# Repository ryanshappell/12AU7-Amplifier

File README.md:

# 12AU7-Amplifier
12AU7 Vacuum tube headphone amplifier.

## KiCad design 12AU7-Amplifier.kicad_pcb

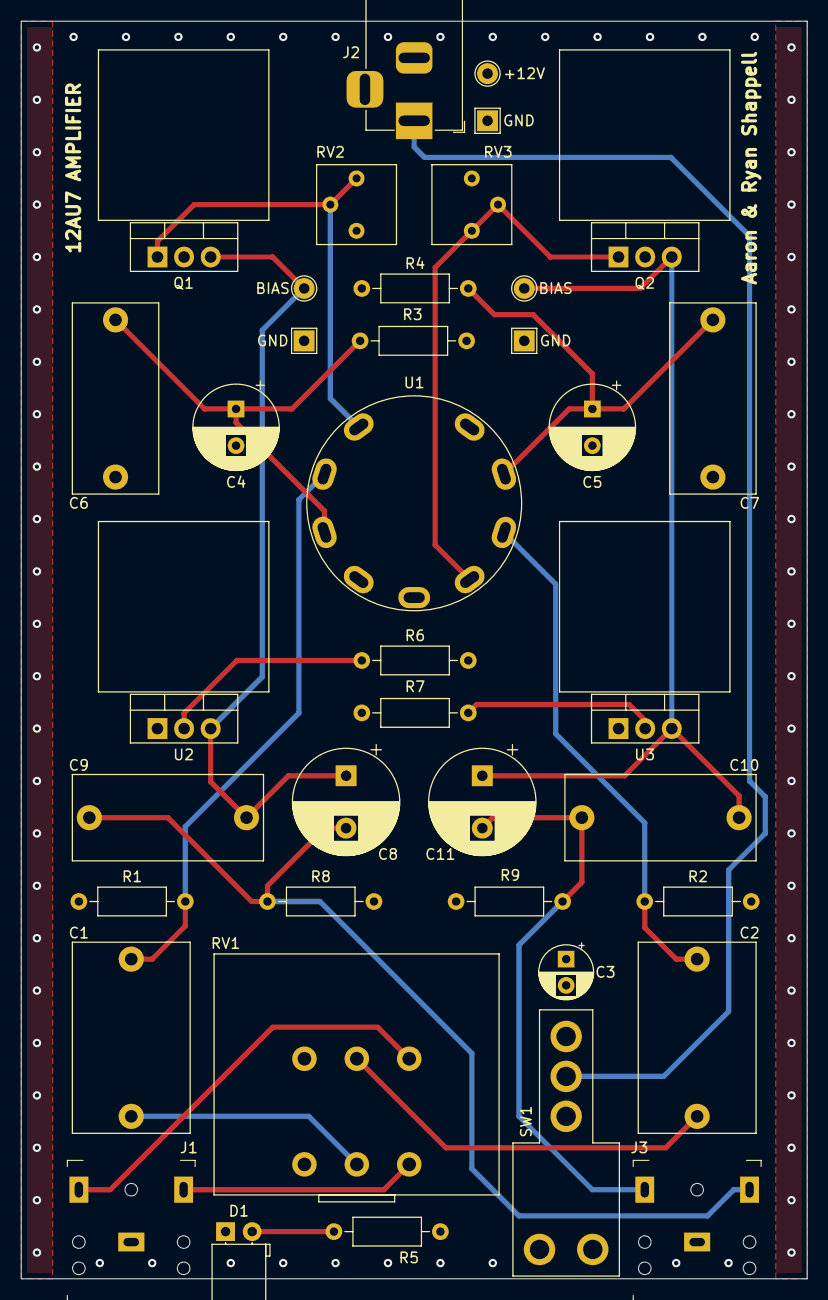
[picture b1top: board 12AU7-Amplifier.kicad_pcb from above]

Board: 4 copper layers, 75.0 x 120.0 mm, 39 parts (0 on the bottom side), 20 nets.

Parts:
C1, C2: 2.2u; C_Rect_L18.0mm_W11.0mm_P15.00mm_FKS3_FKP3
C3: 10uF; CP_Radial_D5.0mm_P2.50mm
C4, C5: 100u; CP_Radial_D8.0mm_P3.50mm
C6, C7, C9, C10: 1u; C_Rect_L18.0mm_W8.0mm_P15.00mm_FKS3_FKP3
C8, C11: 470u; CP_Radial_D10.0mm_P5.00mm
D1: LED; LED_D5.0mm_Horizontal_O1.27mm_Z3.0mm
J1, J3: SJ1-3523N; Headphone_Jack_3.5mm_SJ1-3523N
J2: Barrel_Jack; BarrelJack_Horizontal
Q1, Q2: IRF510; TO-220-3_Vertical
R1, R2: 100k; R_Axial_DIN0207_L6.3mm_D2.5mm_P10.16mm_Horizontal
R3, R4: 150; R_Axial_DIN0207_L6.3mm_D2.5mm_P10.16mm_Horizontal
R5: 470; R_Axial_DIN0207_L6.3mm_D2.5mm_P10.16mm_Horizontal
R6, R7: 10; R_Axial_DIN0207_L6.3mm_D2.5mm_P10.16mm_Horizontal
R8, R9: 1k; R_Axial_DIN0207_L6.3mm_D2.5mm_P10.16mm_Horizontal
RV1: 100k; Alps_100KAX2
RV2, RV3: 10k; CT6EP103
SW1: 100SP1T2B4M7QE
TP1, TP3, TP4: TestPoint; TestPoint_THTPad_2.0x2.0mm_Drill1.0mm
TP2, TP5, TP6: TestPoint; TestPoint_THTPad_D2.0mm_Drill1.0mm
U1: 12AU7
U2, U3: LM317; TO-220-3_Vertical

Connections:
+12V: C3.1, Q1.2, Q2.2, R5.1, RV2.1, RV3.1, SW1.1, TP2.1, U1.4, U1.5
GND: C3.2, C4.2, C5.2, C6.1, C7.2, D1.1, J1.1, J2.2, J2.3, J3.1, R1.1, R2.2, R3.1, R4.1, R6.2, R7.2, R8.2, R9.2, RV1.1, RV1.4, SW1.4, TP1.1, TP3.1, TP4.1, U1.9, U2.1, U3.1
unnamed: C1.1, R1.2, U1.2
unnamed: C1.2, RV1.2
unnamed: C2.1, R2.1, U1.7
unnamed: C2.2, RV1.5
unnamed: C4.1, C6.2, R3.2, U1.3
unnamed: C5.1, C7.1, R4.2, U1.8
unnamed: C8.1, C9.2, Q1.3, TP5.1, U2.3
unnamed: C8.2, C9.1, J3.2, R8.1
unnamed: C10.1, C11.1, Q2.3, TP6.1, U3.3
unnamed: C10.2, C11.2, J3.3, R9.1
unnamed: D1.2, R5.2
unnamed: J1.2, RV1.3
unnamed: J1.3, RV1.6
unnamed: J2.1, SW1.2
unnamed: Q1.1, RV2.2, RV2.3, U1.1
unnamed: Q2.1, RV3.2, RV3.3, U1.6
unnamed: R6.1, U2.2
unnamed: R7.1, U3.2

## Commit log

2019-04-07 Add initial KiCAD files
2019-04-07 finished schematic
2019-04-07 annotate schematic and add power flags
2019-04-08 Assign footprints, create Alps 100KAX2 lib
2019-04-08 fix headphone jack footprint
2019-04-08 fix other jack footprint
2019-04-09 PCB footprint placement
2019-04-09 Remove unused lib
2019-04-09 Add ground plane and trace routing
2019-04-14 Moved the power jack down
2019-04-16 add smoothing capacitor
2019-04-16 reroute and final
2019-04-23 Add title, etc
2020-11-06 Remove plots folder
2020-11-06 Redo schematic and update .gitignore
2020-11-06 Updated page settings
2020-11-06 Reorganize symbol/footprint libraries, add audio jack
2020-11-06 Start on sim
2020-11-06 Add 12au7 spice lib
2020-11-07 Add LM317 spice model
2020-11-07 Simulated one channel for frequency response
2020-11-15 Added components for layout, added 3D models
2020-11-15 Fix resistor values, add parts list
2020-11-16 Move step models to lib, added trimmer pot
2020-11-17 Component layout for Hammond case
2020-11-17 Modify component layout and ALPS footprint silkscreen
2020-11-17 Trace layout, silkscreen, assembly model
2020-11-17 Update parts list
2020-11-23 Add digikey links
2020-11-23 Move step file
2021-01-06 Add gerbers
2021-03-13 Stupid mistake...
2022-10-01 Convert to kicad 6
